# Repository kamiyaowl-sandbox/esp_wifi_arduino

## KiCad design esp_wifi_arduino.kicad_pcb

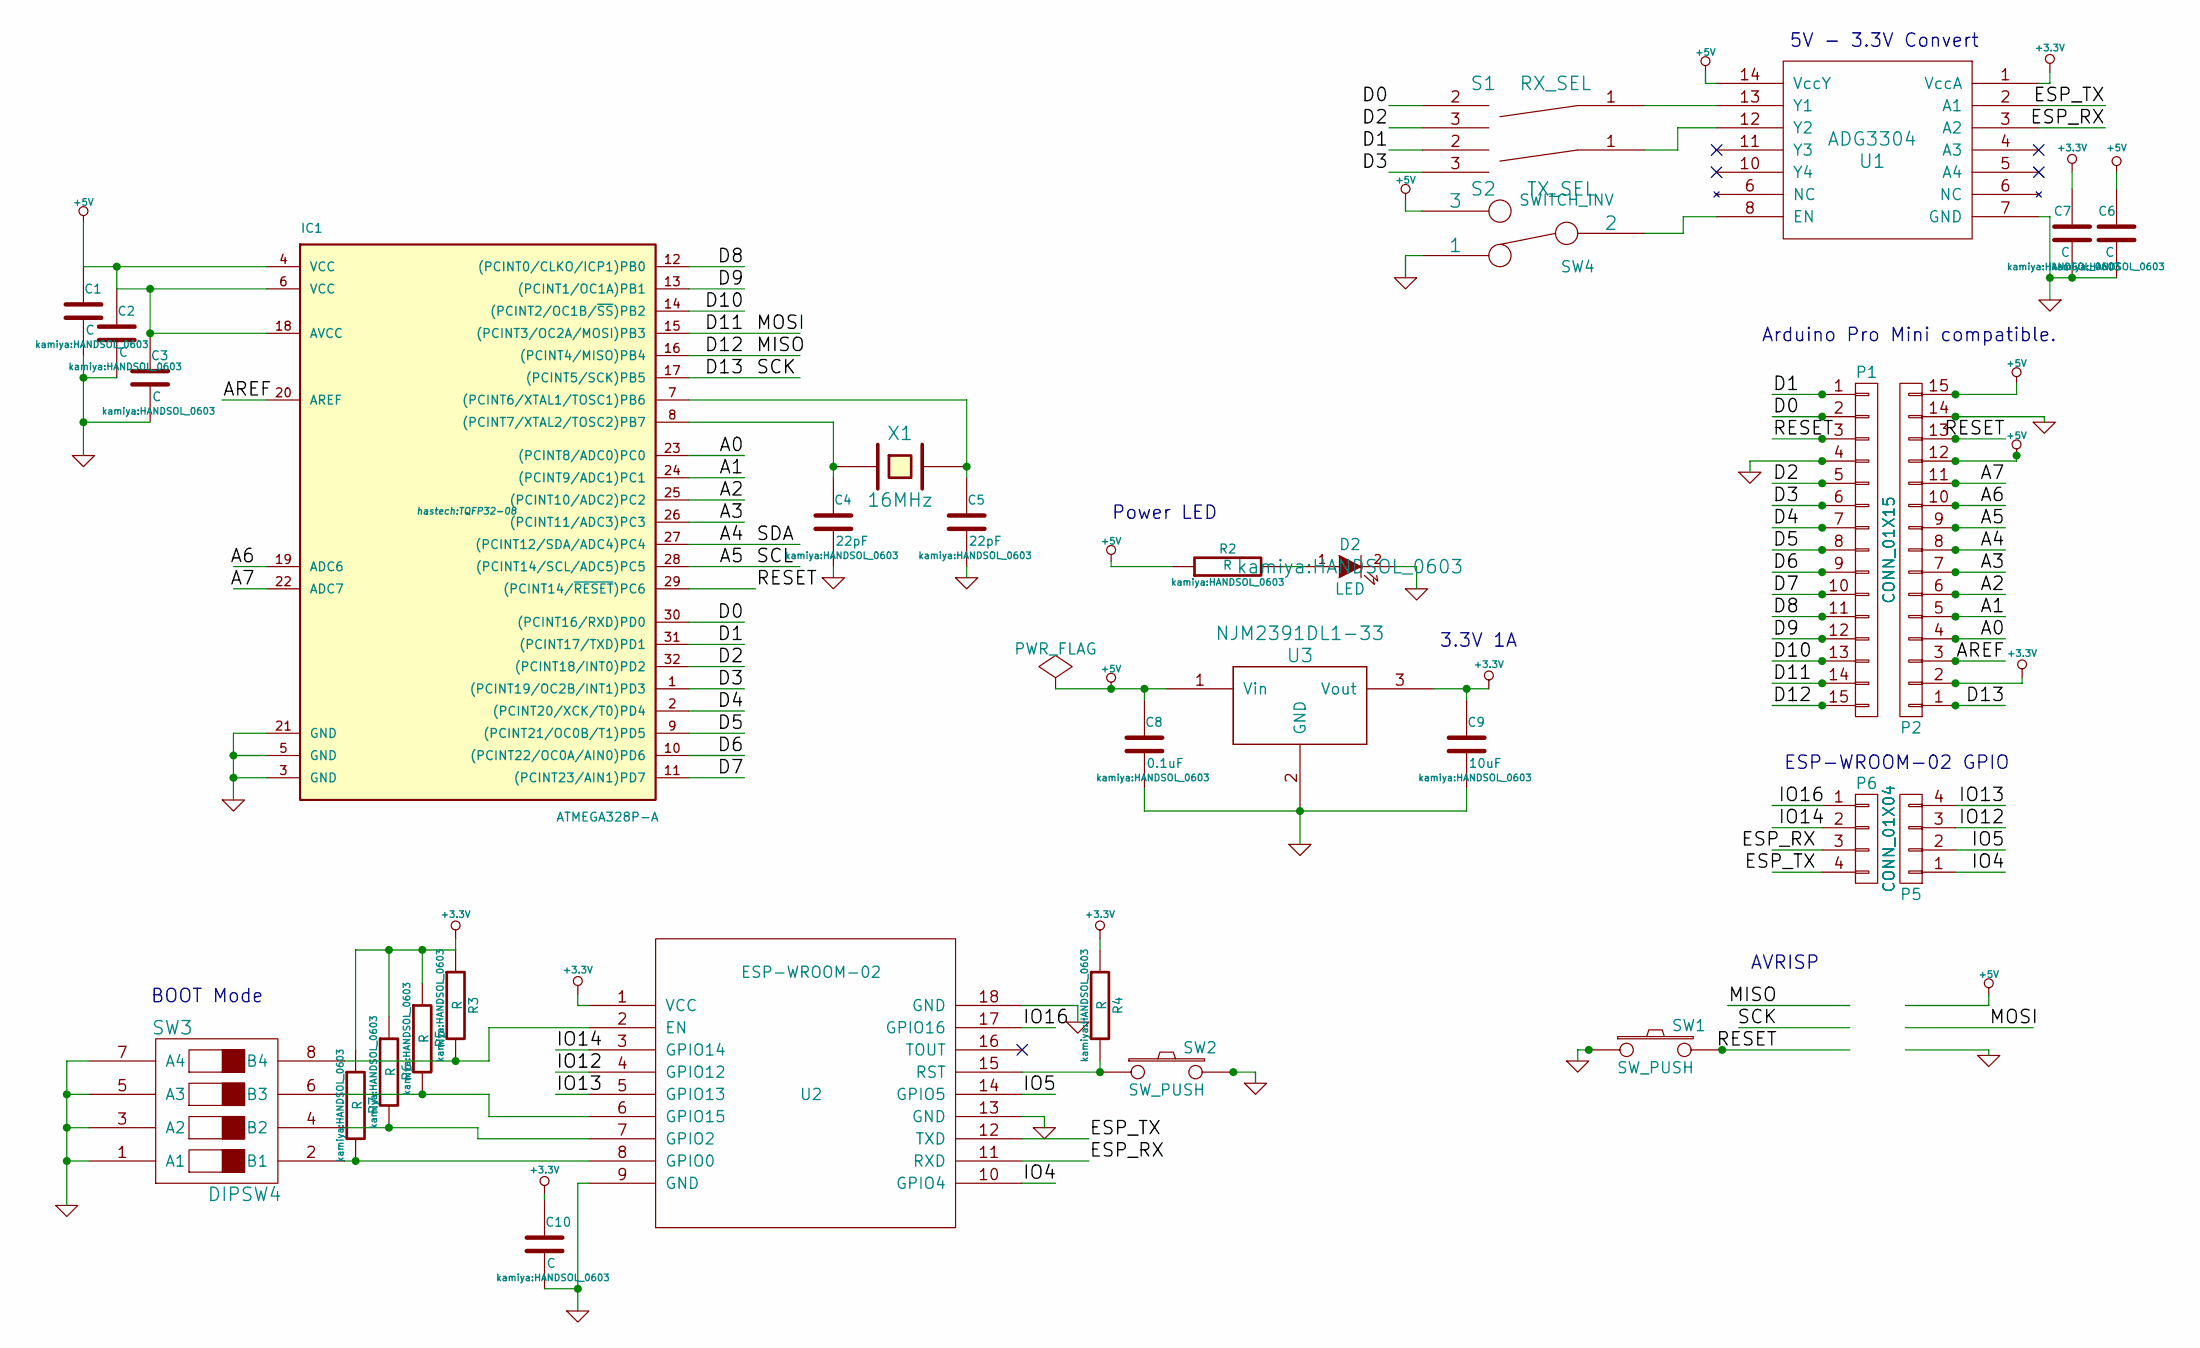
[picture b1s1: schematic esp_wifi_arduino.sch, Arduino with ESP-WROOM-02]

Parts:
C1, C2, C3, C6, C7, C10: C; HANDSOL_0603
C4, C5: 22pF; HANDSOL_0603
C8: 0.1uF; HANDSOL_0603
C9: 10uF; HANDSOL_0603
D2: LED; HANDSOL_0603
IC1: ATMEGA328P-A; TQFP32-08
P1, P2: CONN_01X15; Pin_Header_Straight_1x15
P5, P6: CONN_01X04; Pin_Header_Straight_1x04
R2, R3, R4, R5, R6, R7: R; HANDSOL_0603
S1: RX_SEL; ALPS_SSSS213202(SlideSW)
S2: TX_SEL; ALPS_SSSS213202(SlideSW)
SW1, SW2: SW_PUSH; ALPS_SW_SKRPACE010
SW3: DIPSW4; OTAX_DIPSW4
SW4: SWITCH_INV
U1: ADG3304; AD_TSSOP-14(0.65)
U2: ESP-WROOM-02; ESP_WROOM_02
U3: NJM2391DL1-33; TO-252-3
X1: 16MHz; XTAL_HC-49

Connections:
+3.3V: C7.1, C9.1, C10.1, P2.2, R3.1, R4.1, R5.1, R6.1, R7.1, U1.1 (VccA), U2.1 (VCC), U3.3 (Vout)
+5V: C1.1, C2.1, C3.1, C6.1, C8.1, IC1.4 (VCC), IC1.6 (VCC), IC1.18 (AVCC), P2.12, P2.15, R2.1, SW4.3, U1.14 (VccY), U3.1 (Vin)
/A0: IC1.23 ((PCINT8/ADC0)PC0), P2.4
/A1: IC1.24 ((PCINT9/ADC1)PC1), P2.5
/A2: IC1.25 ((PCINT10/ADC2)PC2), P2.6
/A3: IC1.26 ((PCINT11/ADC3)PC3), P2.7
/A4: IC1.27 ((PCINT12/SDA/ADC4)PC4), P2.8
/A5: IC1.28 ((PCINT14/SCL/ADC5)PC5), P2.9
/A6: IC1.19 (ADC6), P2.10
/A7: IC1.22 (ADC7), P2.11
/AREF: IC1.20 (AREF), P2.3
/D0: IC1.30 ((PCINT16/RXD)PD0), P1.2, S1.2
/D1: IC1.31 ((PCINT17/TXD)PD1), P1.1, S2.2
/D2: IC1.32 ((PCINT18/INT0)PD2), P1.5, S1.3
/D3: IC1.1 ((PCINT19/OC2B/INT1)PD3), P1.6, S2.3
/D4: IC1.2 ((PCINT20/XCK/T0)PD4), P1.7
/D5: IC1.9 ((PCINT21/OC0B/T1)PD5), P1.8
/D6: IC1.10 ((PCINT22/OC0A/AIN0)PD6), P1.9
/D7: IC1.11 ((PCINT23/AIN1)PD7), P1.10
/D8: IC1.12 ((PCINT0/CLKO/ICP1)PB0), P1.11
/D9: IC1.13 ((PCINT1/OC1A)PB1), P1.12
/D10: IC1.14 ((PCINT2/OC1B/~SS~)PB2), P1.13
/D11: IC1.15 ((PCINT3/OC2A/MOSI)PB3), P1.14
/D12: IC1.16 ((PCINT4/MISO)PB4), P1.15
/D13: IC1.17 ((PCINT5/SCK)PB5), P2.1
/ESP_RX: P6.3, U1.3 (A2), U2.11 (RXD)
/ESP_TX: P6.4, U1.2 (A1), U2.12 (TXD)
/IO4: P5.1, U2.10 (GPIO4)
/IO5: P5.2, U2.14 (GPIO5)
/IO12: P5.3, U2.4 (GPIO12)
/IO13: P5.4, U2.5 (GPIO13)
/IO14: P6.2, U2.3 (GPIO14)
/IO16: P6.1, U2.17 (GPIO16)
/RESET: IC1.29 ((PCINT14/~RESET~)PC6), P1.3, P2.13, SW1.2
GND: C1.2, C2.2, C3.2, C4.2, C5.2, C6.2, C7.2, C8.2, C9.2, C10.2, D2.2 (K), IC1.3 (GND), IC1.5 (GND), IC1.21 (GND), P1.4, P2.14, SW1.1, SW2.2, SW3.1 (A1), SW3.3 (A2), SW3.5 (A3), SW3.7 (A4), SW4.1, U1.7 (GND), U2.9 (GND), U2.13 (GND), U2.18 (GND), U3.2 (GND)
unnamed: D2.1 (A), R2.2
unnamed: SW4.2, U1.8 (EN)
unnamed: R4.2, SW2.1, U2.15 (RST)
unnamed: S1.1, U1.13 (Y1)
unnamed: S2.1, U1.12 (Y2)
unnamed: R7.2, SW3.2 (B1), U2.8 (GPIO0)
unnamed: C4.1, IC1.8 ((PCINT7/XTAL2/TOSC2)PB7), X1.1
unnamed: C5.1, IC1.7 ((PCINT6/XTAL1/TOSC1)PB6), X1.2
unnamed: R3.2, SW3.8 (B4), U2.2 (EN)
unnamed: R5.2, SW3.6 (B3), U2.6 (GPIO15)
unnamed: R6.2, SW3.4 (B2), U2.7 (GPIO2)

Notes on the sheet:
Power LED
Arduino Pro Mini compatible.
5V - 3.3V Convert
3.3V 1A
BOOT Mode
AVRISP
ESP-WROOM-02 GPIO

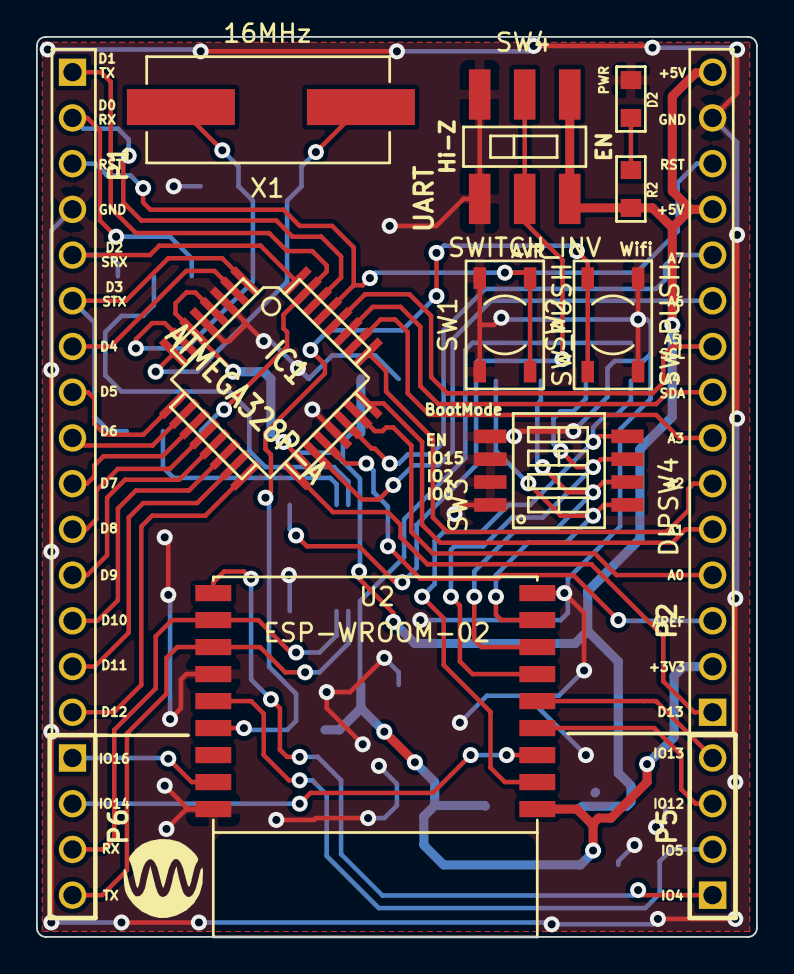
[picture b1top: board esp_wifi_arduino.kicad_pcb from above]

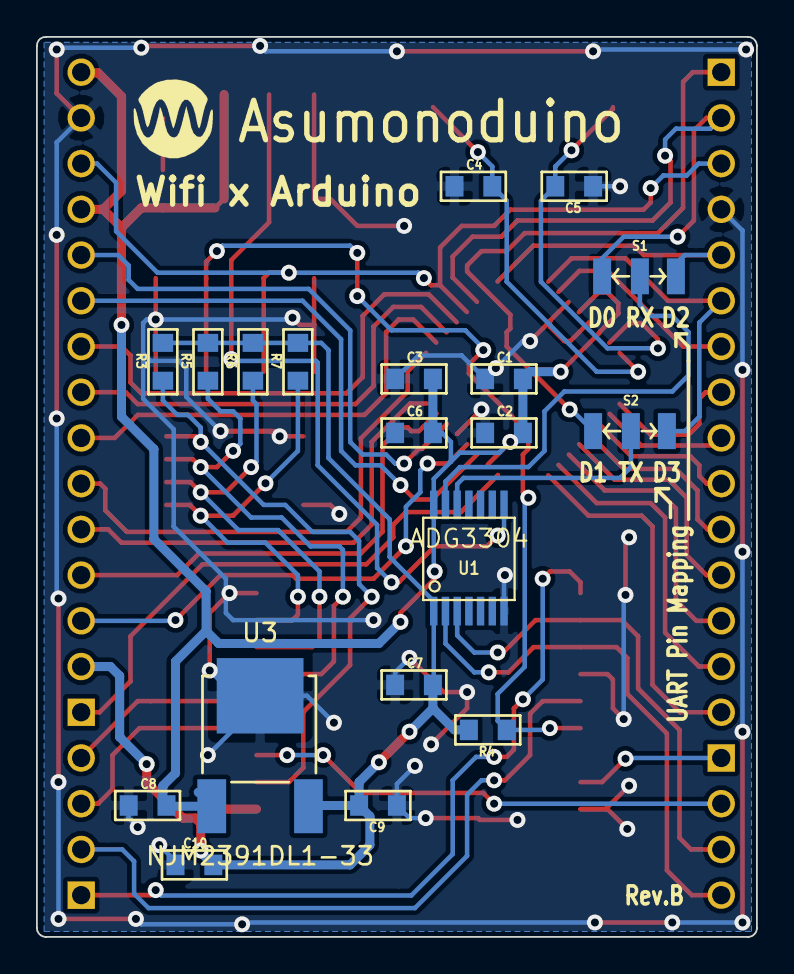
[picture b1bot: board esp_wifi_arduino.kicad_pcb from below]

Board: 2 copper layers, 40.0 x 50.0 mm, 32 parts (19 on the bottom side), 46 nets.

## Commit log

2015-10-24 Create Footprint
2015-10-25 Circuit Create
2015-10-25 Fixed: FaceSilk
2015-10-26 Rev.A
2015-10-29 Create: BOM
2015-11-29 Before Rev.B
2015-11-29 PCB Layout
2015-11-29 Draw Pattern
2015-11-30 Create Production File
2015-12-02 Update Pattern
